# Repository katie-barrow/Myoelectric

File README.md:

PCB Design for EMG sensor controlled prosthetic hand, includes schematic and PCB blueprint to be printed out.

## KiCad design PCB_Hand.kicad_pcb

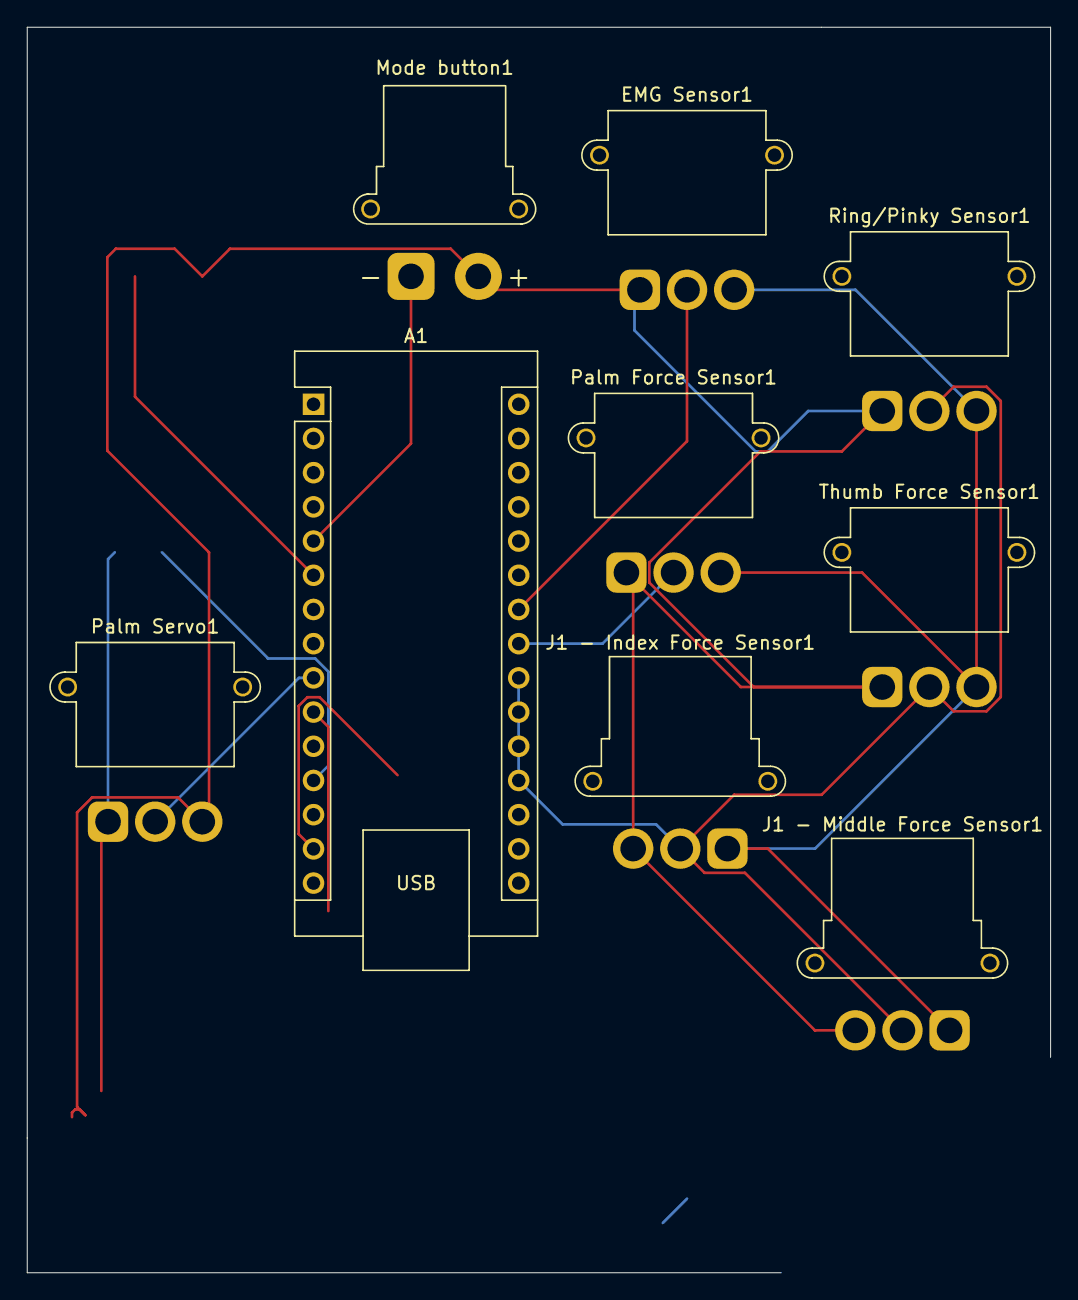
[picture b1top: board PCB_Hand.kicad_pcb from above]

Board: 2 copper layers, 76.0 x 92.5 mm, 9 parts (0 on the bottom side), 7 nets.

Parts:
A1: Arduino_Nano_v3.x; Arduino_Nano
EMG Sensor1: Conn_01x03_Pin; AMASS_MR30PW-M_1x03_P3.50mm_Horizontal
J1 - Index Force Sensor1, J1 - Middle Force Sensor1: Conn_01x03_Pin; AMASS_MR30PW-FB_1x03_P3.50mm_Horizontal
Mode button1: Conn_01x02_Pin; AMASS_XT30PW-F_1x02_P2.50mm_Horizontal
Palm Force Sensor1: Conn_01x03_Pin; AMASS_MR30PW-M_1x03_P3.50mm_Horizontal
Palm Servo1: Conn_01x03_Pin; AMASS_MR30PW-M_1x03_P3.50mm_Horizontal
Ring/Pinky Sensor1: Conn_01x03_Pin; AMASS_MR30PW-M_1x03_P3.50mm_Horizontal
Thumb Force Sensor1: Conn_01x03_Pin; AMASS_MR30PW-M_1x03_P3.50mm_Horizontal

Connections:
+5V: EMG Sensor1.3, J1 - Index Force Sensor1.1, J1 - Middle Force Sensor1.1, Palm Force Sensor1.3, Palm Servo1.1, Ring/Pinky Sensor1.3, Thumb Force Sensor1.3
GND: EMG Sensor1.1, J1 - Index Force Sensor1.3, J1 - Middle Force Sensor1.3, Mode button1.2, Palm Force Sensor1.1, Palm Servo1.3, Ring/Pinky Sensor1.1, Thumb Force Sensor1.1
unnamed: A1.19 (A0), A1.20 (A1), A1.21 (A2), A1.22 (A3), J1 - Index Force Sensor1.2, J1 - Middle Force Sensor1.2, Ring/Pinky Sensor1.2, Thumb Force Sensor1.2
unnamed: A1.23 (A4), Palm Force Sensor1.2
unnamed: A1.24 (A5), EMG Sensor1.2
unnamed: A1.5 (D2), Mode button1.1
unnamed: A1.9 (D6), Palm Servo1.2
